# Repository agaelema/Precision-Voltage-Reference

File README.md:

# Precision Voltage Reference

A simple and efficient instrumentation project of a Precision Voltage Reference. The idea of this project appeared with my passion by the instrumentation and my need of some reference to calibrate my projects involving energy measurement. 

Searching for similar projects I encountered some videos from the Youtube channel "Scullcom Hobby Electronics". This two videos was the kick for my project.
- [Video 1](https://youtu.be/QnH5O-AhqAU?list=PLqnWlo4M8pvoofVfDM7LorucKpwpznr12)
- [Video 2](https://youtu.be/QnH5O-AhqAU?list=PLqnWlo4M8pvoofVfDM7LorucKpwpznr12)

The project is based in the [TI REF102](http://www.ti.com/product/REF102), an 10 V precision voltage reference with maximum tolerance of 0,025% (0.0025 V) in the better model.

Other 4 outputs are derived from the 10 V output, making available 10 V, 5V, 2,50V, 1,125 V and 0,625 V.  This values are obtained using the Precision Difference Amplifier [INA2133](http://www.ti.com/product/INA2133)

The original idea is to be a simple project with components easily found in the market.

### The Supply

The project is powered by a common 5V power bank, and the output of the power bank is applied to a DC/DC step up to 20 V. With one LM317 and one LM337 we generates the positive supply for the REF102 and negative voltage to compensate some offset in the INAs.

The output is referenced to a Virtual ground, not the GND from the power bank.

### The Outputs

Using the INA2133 is possible to implement a 1/2 divider with great precision. At the same time the outputs are buffered between the stages.

To compensate some possible input offset in the stages, was implements simple circuits to externally compensate the offset. This circuit inject some voltage in the Ref pin of the INA.

The ideia of divider:

### The Result

The project was developed using Kicad. The [complet schematic](https://github.com/agaelema/Precision-Voltage-Reference/blob/master/ref-schematic-big.png) is presented bellow.

The assembled board.

The results without calibration (default value), calibrating just the REF102 output and calibrating each output individually.

### Related Articles

There is a serie of 4 articles talking about this project.
- [Article 1 (The idea)](https://www.embarcados.com.br/referencia-de-tensao-de-precisao-a-ideia/)
- [Article 2 (The power supply)](https://www.embarcados.com.br/desenvolvendo-a-fonte-para-referencia-de-precisao/)
- [Article 3 (The voltage reference)](https://www.embarcados.com.br/referencia-de-tensao-da-referencia-de-precisao/)
- [Article 4 (The results)](https://www.embarcados.com.br/resultados-referencia-de-precisao/)

### DISCLAIMER

This project is provided 'as is' with no explicit or implied warranties in respect of its properties, including, but not limited to, correctness and/or fitness for purpose.

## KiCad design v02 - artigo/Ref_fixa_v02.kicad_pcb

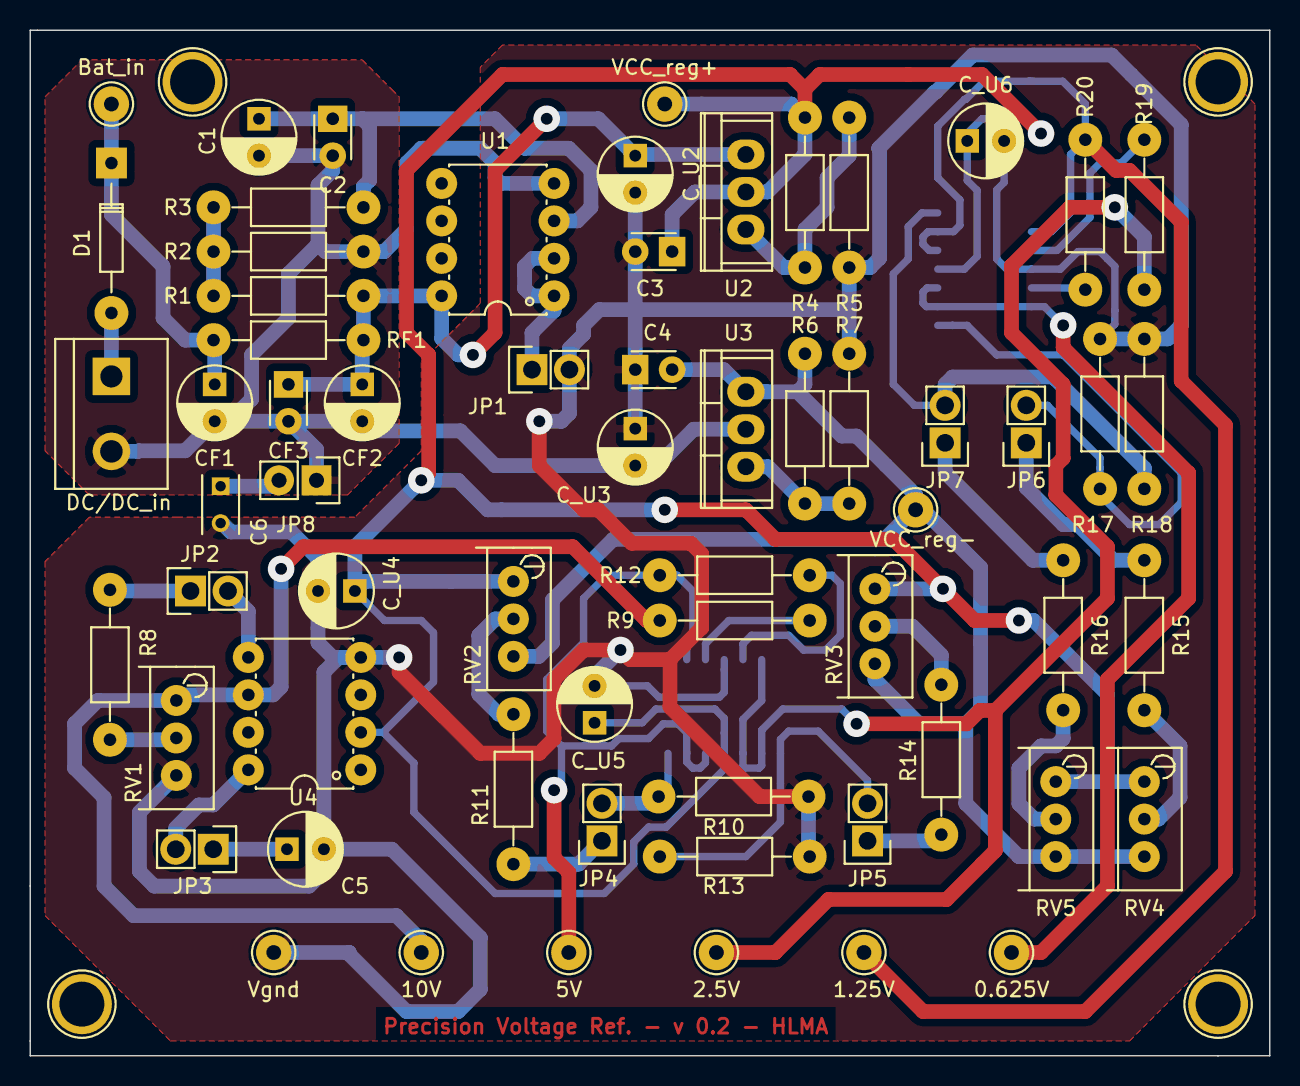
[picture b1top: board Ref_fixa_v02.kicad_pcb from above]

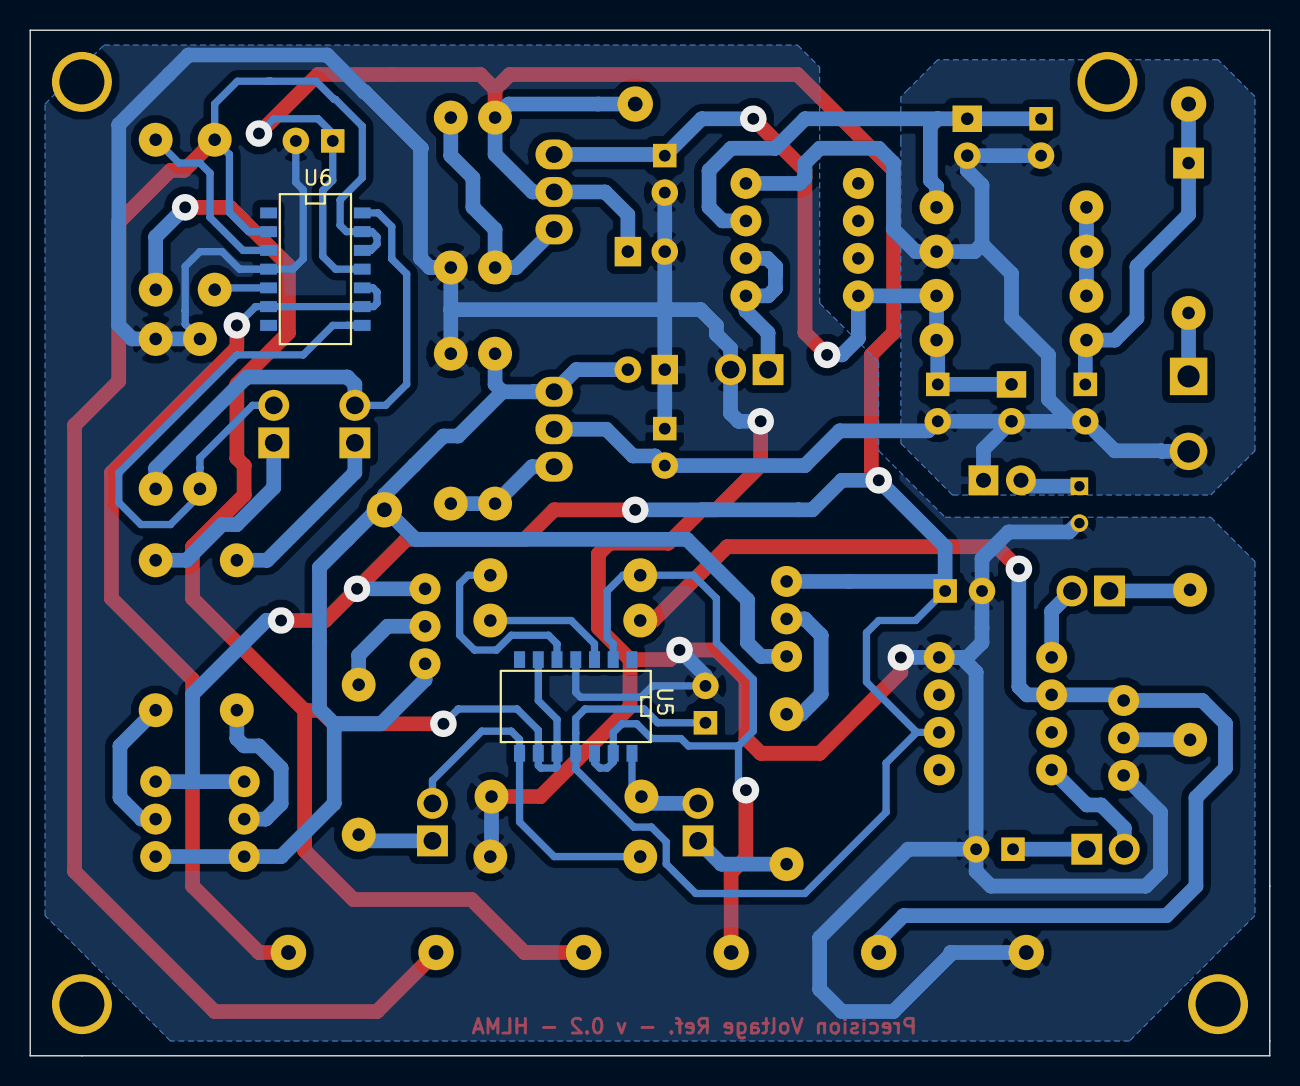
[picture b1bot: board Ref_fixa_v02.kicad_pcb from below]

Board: 2 copper layers, 84.0 x 69.5 mm, 65 parts (2 on the bottom side), 39 nets.

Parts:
0.625V, 1.25V, 2.5V, 5V, 10V: CONN_01X01; PINTST-2.4-1.0mm
Bat_in: CONN_01X01; PINTST-2.4-1.0mm
C1: 10uF; C_Radial_D5_L6_P2.5-1.6mm
C2, C3, C4: 100nF; C_Disc_D3_P2.5-1.8-0.85mm
C5: 1uF; C_Radial_D5_L6_P2.5-1.6mm
C6: 100nF; C_Rect_L4_W2.5_P2.5
CF1: 1uF; C_Radial_D5_L6_P2.5-1.6mm
CF2: 10uF; C_Radial_D5_L6_P2.5-1.6mm
CF3: 100nF; C_Disc_D3_P2.5-1.8-0.85mm
C_U2, C_U3: 10uF; C_Radial_D5_L6_P2.5-1.6mm
C_U4, C_U5, C_U6: 1uF; C_Radial_D5_L6_P2.5-1.6mm
D1: 1N4148; Diode_DO-35_SOD27_Horizontal_RM10-2.1mm
DC/DC_in: 18V-22V; bornier2-edit
JP1, JP2, JP3, JP4, JP5, JP6, JP7: JUMPER; Pin_Header_Straight_1x02-2,1-1,2mm
JP8: JUMPER; Pin_Header_Straight_1x02
R1: 10k; Resistor_Horizontal_RM10mm-2.3-0.85mm
R2: 2k2; Resistor_Horizontal_RM10mm-2.3-0.85mm
R3: 100k; Resistor_Horizontal_RM10mm-2.3-0.85mm
R4, R6: 470; Resistor_Horizontal_RM10mm-2.3-0.85mm
R5: 3k9; Resistor_Horizontal_RM10mm-2.3-0.85mm
R7: 330; Resistor_Horizontal_RM10mm-2.3-0.85mm
R8: 1M; Resistor_Horizontal_RM10mm-2.3-0.85mm
R9, R10, R12, R13, R17, R18, R19, R20: 10; Resistor_Horizontal_RM10mm-2.3-0.85mm
R11, R14, R15, R16: 1.2k; Resistor_Horizontal_RM10mm-2.3-0.85mm
RF1: 22; Resistor_Horizontal_RM10mm-2.3-0.85mm
RV1: 20k; Potentiometer-pinlinear-2.1-0.85mm
RV2, RV3, RV4, RV5: 100k; Potentiometer-pinlinear-2.1-0.85mm
U1: LM358; PDIP-8-3d-2.1-0.85mm
U2: LM317AT; TO-220-3d
U3: LM337T; TO-220-3d
U4: REF102BP; PDIP-8-3d-2.1-0.85mm
U5, U6: INA2133UA; SOIC-14_N-0.75mm
VCC_reg+: CONN_01X01; PINTST-2.4-1.0mm
VCC_reg-: CONN_01X01; PINTST-2.4-1.0mm
Vgnd: CONN_01X01; PINTST-2.4-1.0mm

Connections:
GNDREF: JP1.1, U1.1, U1.2
unnamed: Bat_in.1, CF1.1, D1.1, RF1.2
unnamed: C1.1, C2.1, R3.1, U1.3
unnamed: C5.1, JP3.1
unnamed: C6.1, JP8.2
unnamed: D1.2, DC/DC_in.1
unnamed: JP2.1, R8.1
unnamed: JP2.2, U4.5
unnamed: JP3.2, U4.8
unnamed: JP4.1, R11.1
unnamed: JP4.2, R10.1, U5.14
unnamed: JP5.1, R14.1
unnamed: JP5.2, R13.1, U5.8
unnamed: JP6.1, R15.1
unnamed: JP6.2, R17.1, U6.8
unnamed: JP7.1, R16.1
unnamed: JP7.2, R18.1, U6.14
unnamed: R1.1, R2.2, R3.2
unnamed: R4.1, R5.2, U2.1
unnamed: R6.2, R7.1, U3.1
unnamed: R8.2, RV1.2
unnamed: R9.1, U5.3
unnamed: R11.2, RV2.2
unnamed: R12.1, U5.5
unnamed: R14.2, RV3.2
unnamed: R15.2, RV4.2
unnamed: R16.2, RV5.2
unnamed: R19.1, U6.3
unnamed: R20.1, U6.5
Vcc+: CF2.1, CF3.1, C_U2.1, R1.2, RF1.1, U1.8, U2.3
Vcc-: C1.2, C2.2, CF1.2, CF2.2, CF3.2, C_U3.2, DC/DC_in.2, JP8.1, R2.1, U1.4, U3.2
Vcc_reg+: C3.1, C_U4.1, C_U5.1, C_U6.1, R4.2, RV2.1, RV3.1, RV4.1, RV5.1, U2.2, U4.2, U5.11, U6.11, VCC_reg+.1
Vcc_reg-: C4.2, R6.1, RV2.3, RV3.3, RV4.3, RV5.3, U3.3, VCC_reg-.1
Vgnd: C3.2, C4.1, C5.2, C6.2, C_U2.2, C_U3.1, C_U4.2, C_U5.2, C_U6.2, JP1.2, R5.1, R7.2, R10.2, R13.2, R17.2, R18.2, RV1.3, U4.4, U5.4, U6.4, Vgnd.1
ref_0.625V: 0.625V.1, U6.6, U6.9, U6.10
ref_1.25V: 1.25V.1, R20.2, U6.2, U6.12, U6.13
ref_2.5V: 2.5V.1, R19.2, U5.6, U5.9, U5.10
ref_5V: 5V.1, R12.2, U5.2, U5.12, U5.13
ref_10V: 10V.1, R9.2, RV1.1, U4.6

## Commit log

2016-09-06 Readme minor changes
2016-09-07 Changes in values
    Change in R7 value, from 330 to 100. Change the voltage from -2.13 to
    -1.52
2017-04-19 Readme changes
2017-08-15 ### DISCLAIMER
2017-12-06 change
